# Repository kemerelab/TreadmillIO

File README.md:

# TreadmillIO

The TreadmillIO project (which needs a better name!) combines a simple USB-based
data IO module with a Python framework to provide a way to control behavioral
experiments using a simple YAML-based configuration scheme. One particular focus
of the project is to receive input from a rotary encoder to control auditory 
stimuli in a VR environment, but it is also convenient to use for experiments in
freely moving animals. In conjunction with the 
[PyRenderMaze project](http://github.com/ckemere/PyRenderMaze), a simple OpenGL-based
visual VR environment can easily be deployed. 

Some sample sound stimuli can be found in the [simple-sound-stimuli](https://github.com/kemerelab/simple-sound-stimuli)
repository.

### Requirements
The software is currently tested on Ubuntu Linux. The low-latency audio framework
relies on ALSA, which is Linux only, and the UVC WebCam capture interface has
only been tested on Linux. However, the project should otherwise work across
platforms. Pull requests for Windows or MAC compiling are welcome.

See the [installation instructions for the software framework](Documentation/Installation/INSTALL.md) to get up
and running.

### Configuring tasks controlled with the Treadmill-IO module

Some example [configuration files](Software/ExampleConfigFiles/) are available.

An example experimental setup using PschoPy-based stimuli is in the 
[simple-pyschopy-visual-task](https://github.com/kemerelab/simple-psychopy-visual-task)
project.

<!-- 
## Auditory VR Tasks

The file `AuditoryVR.py` generates a behavioral control system which has the following abilities:
  - Logs data acquired from the IO module
  - Processes incoming rotational encoder data to map wheel position to virtual position
  - Presents auditory stimuli in one of three modalities: background sounds, cues triggered by task states, and the sound of acoustic landmarks (which are amplitude modulated by their distance to the mouse in virtual space)
  - Responds appropriately to GPIO inputs (i.e., licks) based on task logic
  - Triggers GPIO output pulses as appropriate (i.e., to drive a syringe pump)

The controller is configued by a YAML file. An example configuration file, with explanatory comments is below.

```yaml
Info: # "Info" configuration options can be overridden by command line options
  MouseID: V1A1 # Used to name saved data file
  Note: '' # Added in a block at the start of saved data file
  Session: '' # This is added to default (date and time)
  TaskType: 3tones-change-classical

Preferences:
  HeartBeat: 250 # The interval at which a heart-beat info message is printed to screen (in ms) 

GPIO: # A list of GPIO pins used in the task
  Lick: # This is an arbitrary label used later to configure Reward
    Number: 3 # This is the pin number from the board
    Type: 'Input_Pulldown' # Pin type is either 'Inout' or 'Output'; special cases could be 'Input_Pulldown' or 'Input_Pullup' 
                           # (where the pull-down/pull-up resistors are enabled).
    Power: True # The 'Power' option is for 'Input' type GPIOs. It configures whether the Aux-GPIO is set to high, 
                # enabling the power channel of the audio jack.
  Reward:
    Number: 4
    Type: 'Output'
    Mirror: True # The 'Mirror' option is for 'Output' type GPIOs. It configures whether the associated Aux-GPIO pin is raised/lowered 
                 # whenver the GPIO itself is. The Aux-GPIO is connected to an LED, which allows for visualization of the GPIO state.

Maze:
  Type: 'VR' # VR or physical
  EncoderGain: 4096.0 # Encoder value per revolution
  Length: 150.0 # Length of the track. Presumably in cm units, but units don't really matter as long as they're consistent.
  WheelDiameter: 20.2 # Diameter of the wheel (presumably in cm units).
  TrackTransform: None # Not currently implemented.

AuditoryStimuli:
  AudioFileDirectory: '/home/ckemere/Code/TreadmillTracker/ClientSide/Tasks/HeadFixedTask/Sounds' # Directory in which file is stored
  MaximumNumberOfStimuli: 10 # Maximum number of auditory stimuli which follow in the StimuliList
  OscPort: 12345 # TCP port to use for OSC communication with jackminimix
  Defaults: # Default values for stimulus parameters
    Filename: '' # Possible to specify a default sound file
    BaselineGain: 0.0 # Volume of stimulus. Corresponds to the peak volume for a 'Localized' stimulus 
    OffGain: -90.0 # dB for stimulus off. -90 dB corresponds to 0 for jackminimix
    Type: 'Localized' # 'Localized' (landmark), 'Background', or 'Beep'
    Modulation: # Parameters which define how 'Localized' stimuli are spatially-modulated
      Type: Linear # Currently only 'Linear'
      CenterPosition: 0.0 # Position of Localized stimulus in VR space
      Width: 25 # cm in which sound is on (full width)
      #Rate: -20.0 # dB/cm - NOT CURRENTLY IMPLEMENTED BUT WOULD BE NICE FOR THE FUTURE
      CutoffGain: -60.0 #dB at cutoff - The change in gain as a function of position is determined
                        #  by the Width, BaselineGain, and CutoffGain parameters.
                        #  Note that true "Off" corresponds in our system to -90 dB.
                        #  So depending on SNR and perceptual ability, a CutoffGain greater
                        #  than that value might be noticeable.

  StimuliList:
    BackgroundSound: # This label is abitrary. In the case of "Beep" stimuli, it is used to configure Reward
      MinimixInputPort: 1 # jackminimix channel to use. By default, these will be auto-assigned if not specified
      MinimixChannel: 'left' # stereo audio channel whose volume should be controlled for this stimulus
      Type: 'Background' # Stimuli type - 'Localized', 'Background', or 'Beep'
      BaselineGain: -5.0
      Filename: 'pink_noise.wav'
      Color: 'pink' # Matplotlib color name used for visualization system
    Zone_1:
      CenterPosition: 12.5 
      Filename: 'tone_3kHz.wav'
      Modulation:
        Width: 10
      Color: 'lime'
    Zone_2:
      CenterPosition: 102.5 
      Filename: 'tone_11kHz.wav'
      Modulation:
        Width: 25
      Color: 'orange'
    RewardSound:
      Type: 'Beep'
      Filename: 'tone_11kHz.wav'
      Duration: 250 # ms

RewardZones: # Configuration of Reward locations
  RewardZoneList:
    Reward1: # Arbitrary label
      Type: 'Operant' # Currently either "Classical" or "Operant" corresponding to
                      # the definitions from psychology. Classical rewards are delivered
                      # at a particular location regardless of animal behavior. Operant
                      # rewards require a GPIO trigger (which we call a "Lick")
      LickPin: 'Lick' # Label of GPIO for sensor which triggers reward (in the case of Operant-style tasks)
      DispensePin: 'Reward' # (Required!) Label of GPIO for output pin which should trigger reward dispensing. 
      PumpRunTime: 1000 # How long to run the reward pump for. Note that this is also the duration
                        # of time that any associated Beep will be played.
      LickTimeout: 3000.0 # Time between reward availability
      MaxSequentialRewards: 50 # Number of times an animal that has stopped in the reward zone
                               # can be rewarded without having to exit and re-enter. After reaching
                               # this number of rewards, the animal has to pass through the "ResetZone"
                               # to reset reward availability.
      RewardZoneStart: 145 # The reward location begins at this point (in track coordinates).
                        # Note that since the track loops around, the end can be before the 
                        # beginning. (Order of beginning and end matter!)
      RewardZoneEnd: 30 # The reward zone ends at this point.
      ResetZoneStart: 100 # The start of location of the zone in the track that primes this reward location.
      ResetZoneEnd: 130 # The end of the reset zone.
      Color: 'black' # Visualization color of the reward zone.
      RewardSound: 'RewardSound' # The name of the auditory stimulus (of type "Beep") which should be played 
                                 # at the time of reward. This plays for the same duration of the pulse which
                                 # triggers the pump.

```

## StateMachine or VisualStimulus Tasks
The file `VisualStimulusExperiment.py` executes a state machine. Critically one of the states sends commands to a 
visual stimulus server started by executing `VisualStimulusServer.py`. Currently, the `VisualStimulusServer.py` file
creates a grey screen and presents a flashing checkerboard either in the left or right visual hemifields (calibrated
for a large 40" curved display). Following is an example YAML configuration file:

```
Info: # "Info" configuration options can be overridden by command line options
  MouseID: V1A1 # Used to name saved data file
  Note: '' # Added in a block at the start of saved data file
  Session: '' # This is added to default (date and time)
  TaskType: Moana Classical Conditioning

Preferences:
  HeartBeat: 1000 # The interval at which a heart-beat info message is printed to screen (in ms) 
  AudioFileDirectory: '/home/ckemere/Code/TreadmillTracker/ClientSide/Tasks/HeadFixedTask/Sounds' # Directory in which file is stored
  RandomSeed: 345
  VisualCommsPort: 5556
  LogCommands: True

GPIO: # A list of GPIO pins used in the task
  Camera: # This is an arbitrary label used later to configure Reward
    Number: 1 # This is the pin number from the board
    Type: 'Input_Pulldown' 
    Power: False
  Lick: # This is an arbitrary label used later to configure Reward
    Number: 2 # This is the pin number from the board
    Type: 'Input_Pulldown' # Pin type is either 'Input' or 'Output'; special cases could be 'Input_Pulldown' or 'Input_Pullup' 
                           # (where the pull-down/pull-up resistors are enabled).
    Power: True # The 'Power' option is for 'Input' type GPIOs. It configures whether the Aux-GPIO is set to high, 
                # enabling the power channel of the audio jack.
  ScreenLeft: # This is an arbitrary label used later to configure Reward
    Number: 3 # This is the pin number from the board
    Type: 'Input_Pulldown' 
    Power: True

  ScreenRight: # This is an arbitrary label used later to configure Reward
    Number: 4 # This is the pin number from the board
    Type: 'Input_Pulldown' 
    Power: True
  Reward:
    Number: 5
    Type: 'Output'
    Mirror: True # The 'Mirror' option is for 'Output' type GPIOs. It configures whether the associated Aux-GPIO pin is raised/lowered 
                 # whenver the GPIO itself is. The Aux-GPIO is connected to an LED, which allows for visualization of the GPIO state.
  GreyScreenIO:
    Number: 6
    Type: 'Output'
    Mirror: True 
  Disable7:
    Number: 7
    Type: 'Input_Disable'
  Disable8:
    Number: 8
    Type: 'Input_Disable'
  Disable9:
    Number: 9
    Type: 'Input_Disable'
  Disable10:
    Number: 10
    Type: 'Input_Disable'
  Disable11:
    Number: 11
    Type: 'Input_Disable'
  Disable12:
    Number: 12
    Type: 'Input_Disable'              

Maze:
  Type: 'StateMachine'

StateMachine: # Note - will start at the state below with the parameter "FirstState: True". Otherwise
              # the first state listed will be first.
  BlankScreen:
    Type: 'Visualization'
    Params:
      VisType: 'Fixed' # Can be either "Fixed" or "Random"
      Command: 'GREY'  # Command string sent to VisualStimulusServer
    NextState: 'Raise'
  Raise: # Raise a GPIO during the grey screen period
    Type: 'SetGPIO'
    Params:
      Pin: 'GreyScreenIO'
      Value: 1
    NextState: 'Intertrial'
  Intertrial:
    Type: 'Delay'
    Params:
      Duration: 'Fixed' # Can be either "Fixed" or "Random"
      Value: 5000
    NextState: 'Lower'
  Lower:
    Type: 'SetGPIO'
    Params:
      Pin: 'Reward'
      Value: 0
    NextState: 'StimulusPresentation'
  StimulusPresentation:
    FirstState: True    # Start statemachine here!s
    Type: 'Visualization'
    Params:
      VisType: 'Random' # Random visualizations are currently uniformly distributed based on the specified
                        # relative probabilities.
      Options:
        Right:
          Command: 'RIGHT' # Command sent to VisualStimulusServer
          Probability: 1   # Relative probabilitity. These will be normalized by the sum of all options.
        Left:
          Command: 'LEFT'
          Probability: 1
    NextState: 'StimulusPresentationDelay'
  StimulusPresentationDelay:
    Type: 'Delay'
    Params:
      Duration: 'Exponential' # Random duration is a bounded exponential.
      Rate: 1000              # Rate of exponential distribution in ms.
      Min: 2000               # Minimum value added to samples from distribution.
      Max: 4000               # All samples are truncated to this value.
    NextState: 'Reward'
  Reward:
      Type: 'Reward'   # We could also trigger reward by using the SetGPIO command. The "Reward" states
                       # are 'non-blocking', meaning the state machine will move along to the next state.
      NextState: 'BlankScreen'
      Params:
        DispensePin: 'Reward' # (Required!) Label of GPIO for output pin which should trigger reward dispensing. 
        PumpRunTime: 100 # How long to run the reward pump for. Note that this is also the duration
                          # of time that any associated Beep will be played.
        RewardSound: 'RewardSound' # The name of the auditory stimulus (of type "Beep") which should be played 
                              # at the time of reward. This plays for the same duration of the pulse which
                              # triggers the pump.

AuditoryStimuli:
  Defaults: # Default values for stimulus parameters
    Filename: '' # Possible to specify a default sound file
    BaselineGain: 0.0 # Volume of stimulus. Corresponds to the peak volume for a 'Localized' stimulus 
    Type: 'Localized' # 'Localized' (landmark), 'Background', or 'Beep'
    Modulation: # Parameters which define how 'Localized' stimuli are spatially-modulated
      Type: Linear # Currently only 'Linear'
      CenterPosition: 0.0 # Position of Localized stimulus in VR space
      Width: 25 # cm in which sound is on (full width)
      #Rate: -20.0 # dB/cm - NOT CURRENTLY IMPLEMENTED BUT WOULD BE NICE FOR THE FUTURE
      CutoffGain: -60.0 #dB at cutoff - The change in gain as a function of position is determined
                        #  by the Width, BaselineGain, and CutoffGain parameters.
                        #  Note that true "Off" corresponds in our system to -90 dB.
                        #  So depending on SNR and perceptual ability, a CutoffGain greater
                        #  than that value might be noticeable.  

  StimuliList:
    BackgroundSound: # This label is abitrary. In the case of "Beep" stimuli, it is used to configure Reward
      Type: 'Background' # Stimuli type - 'Localized', 'Background', or 'Beep'
      BaselineGain: -5.0
      Filename: 'pink_noise.wav'
      Color: 'pink' # Matplotlib color name used for visualization system
    RewardSound:
      Type: 'Beep'
      Filename: 'tone_11kHz.wav'
```

## Camera Window
At high resolution (>= 1080p) and frame rate, the multiprocessing queue (and underlying pipe) for the camera window struggles to pickle/unpickle the image data quickly enough to keep up with webcam stream (the write process, which uses raw jpeg data, doesn't seem to have this issue, presumably because serialization of the raw data is trivial). To manage this issue, we can specify a maximum buffer size for the queue. When exceeded, the queue will stop receiving new frames from the send end (`CameraInterface`) until the receive end (`CameraWindow`) has flushed the queue. This leads to some push and pull, periods of normal streaming interrupted by pauses, so there's room for improvement. An example config for a 1080p webcam:

```yaml
Cameras:
  Camera1:
    RecordVideo: True
    FilenameHeader: 'MouseCam1'
    Compress: False # Sets whether to transcode the MJPEG which comes from the camera to H.264
    CameraIndex: 0
    ResX: 1920 
    ResY: 1080
    FrameRate: 30
    BufferSizeFrames: 30 # maximum frames to buffer before flushing queue
    #BufferSizeMB: 500 # we could instead specify buffer size by MB
    Verbose: False
    CameraParams:
      Power Line frequency: 2, # 60 Hz
      Gain: 10
``` -->

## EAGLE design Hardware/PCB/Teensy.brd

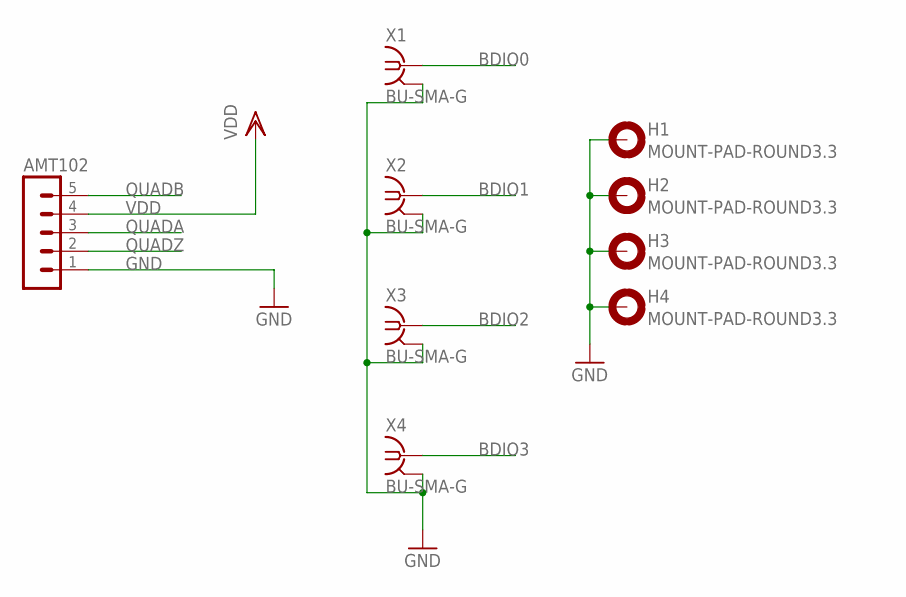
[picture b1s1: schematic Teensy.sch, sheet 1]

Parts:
AMT102: MA05-1
H1, H2, H3, H4: MOUNT-PAD-ROUND3.3; 3,3-PAD
X1, X2, X3, X4: BU-SMA-G

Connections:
BDIO0: X1.1; also elsewhere on the board
BDIO1: X2.1; also elsewhere on the board
BDIO2: X3.1; also elsewhere on the board
BDIO3: X4.1; also elsewhere on the board
GND: AMT102.1, H1.B3,3, H2.B3,3, H3.B3,3, H4.B3,3, X1.2, X1.3 (2), X1.4 (2), X1.5 (2), X2.2, X2.3 (2), X2.4 (2), X2.5 (2), X3.2, X3.3 (2), X3.4 (2), X3.5 (2), X4.2, X4.3 (2), X4.4 (2), X4.5 (2); also elsewhere on the board
QUADA: AMT102.3; also elsewhere on the board
QUADB: AMT102.5; also elsewhere on the board
QUADZ: AMT102.2; also elsewhere on the board
VDD: AMT102.4; also elsewhere on the board

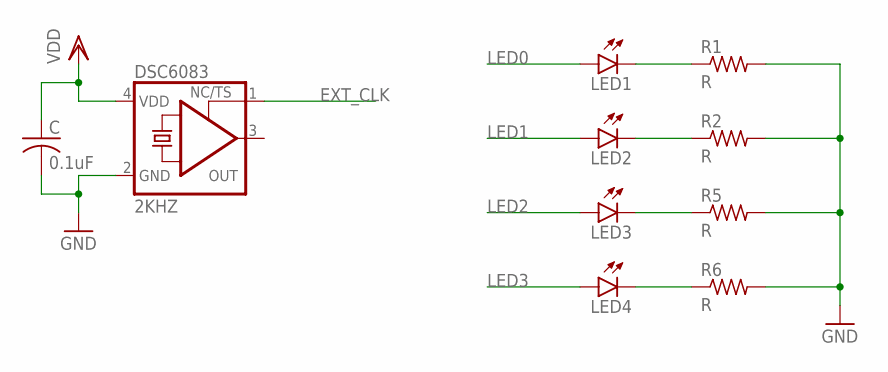
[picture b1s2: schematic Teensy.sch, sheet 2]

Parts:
C: 0.1uF; C0603
DSC6083: 2KHZ; 3.2X2.5_KXO-V96
LED1: LEDCHIPLED_0603; CHIPLED_0603
LED2, LED3, LED4: LEDCHIP-LED0603; CHIP-LED0603
R1, R2, R5, R6: R; R0603

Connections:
EXT_CLK: DSC6083.1 (TS); also elsewhere on the board
GND: C.2, DSC6083.2 (GND), R1.2, R2.2, R5.2, R6.2; also elsewhere on the board
LED0: LED1.A; also elsewhere on the board
LED1: LED2.A; also elsewhere on the board
LED2: LED3.A; also elsewhere on the board
LED3: LED4.A; also elsewhere on the board
unnamed: LED1.C, R1.1
unnamed: LED2.C, R2.1
unnamed: LED3.C, R5.1
unnamed: LED4.C, R6.1
VDD: C.1, DSC6083.4 (VDD); also elsewhere on the board

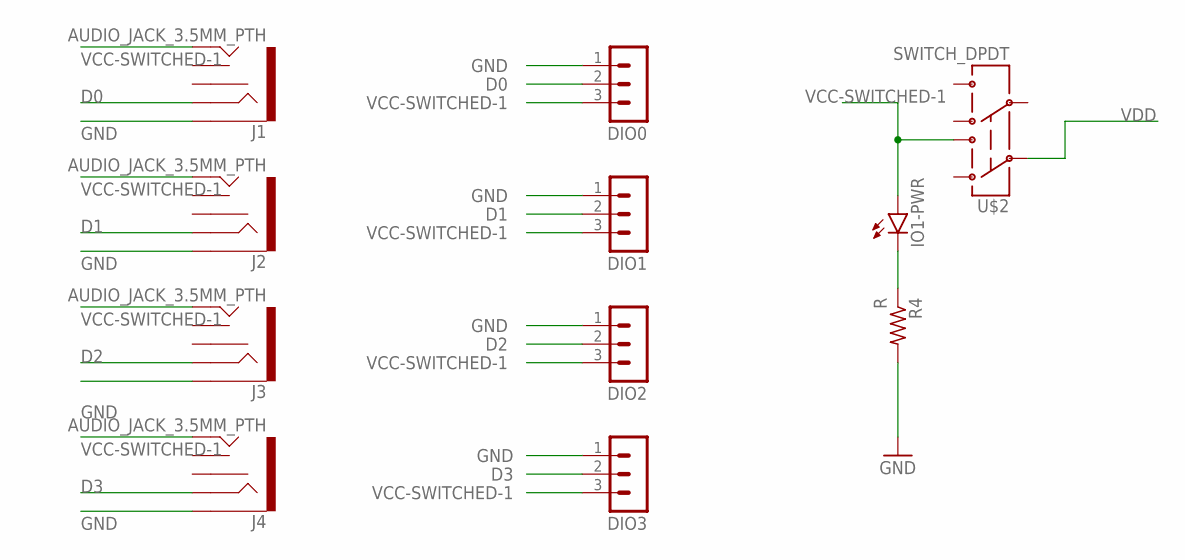
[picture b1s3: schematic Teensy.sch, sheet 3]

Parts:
DIO0, DIO1, DIO2, DIO3: MA03-1
IO1-PWR: LEDCHIP-LED0603; CHIP-LED0603
J1, J2, J3, J4: AUDIO_JACK_3.5MM_PTH; AUDIO-JACK
R4: R; R0603
U$2: SWITCH_DPDT; JS_DPDT_TH

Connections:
D0: DIO0.2, J1.RING; also elsewhere on the board
D1: DIO1.2, J2.RING; also elsewhere on the board
D2: DIO2.2, J3.RING; also elsewhere on the board
D3: DIO3.2, J4.RING; also elsewhere on the board
GND: DIO0.1, DIO1.1, DIO2.1, DIO3.1, J1.SLEEVE, J2.SLEEVE, J3.SLEEVE, J4.SLEEVE, R4.2; also elsewhere on the board
unnamed: IO1-PWR.C, R4.1
VCC-SWITCHED-1: DIO0.3, DIO1.3, DIO2.3, DIO3.3, IO1-PWR.A, J1.TIP, J2.TIP, J3.TIP, J4.TIP, U$2.3
VDD: U$2.2; also elsewhere on the board

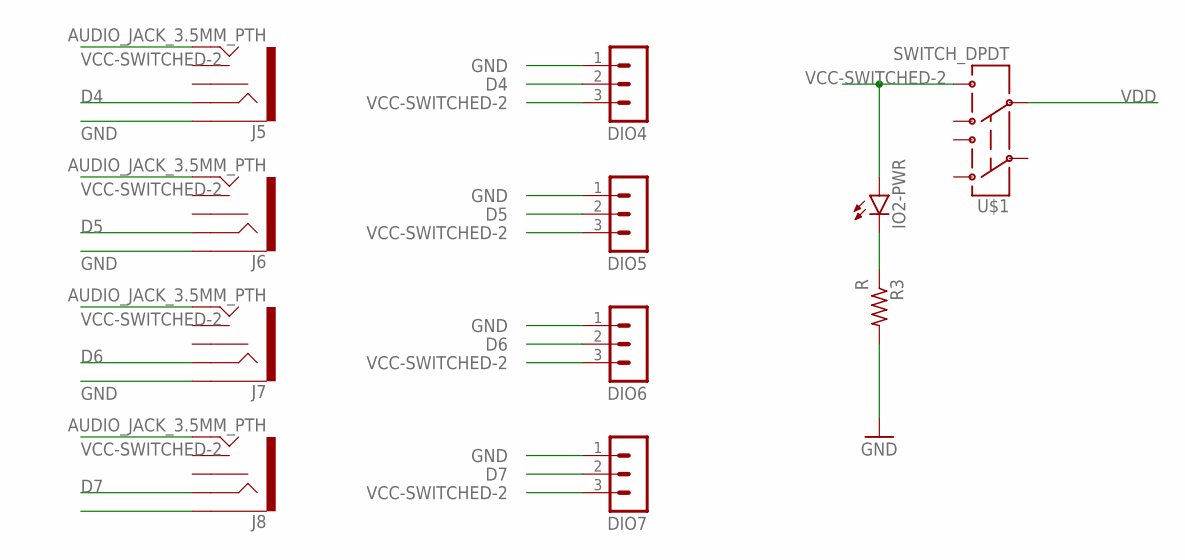
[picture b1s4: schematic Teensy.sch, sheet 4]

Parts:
DIO4, DIO5, DIO6, DIO7: MA03-1
IO2-PWR: LEDCHIP-LED0603; CHIP-LED0603
J5, J6, J7, J8: AUDIO_JACK_3.5MM_PTH; AUDIO-JACK
R3: R; R0603
U$1: SWITCH_DPDT; JS_DPDT_TH

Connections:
D4: DIO4.2, J5.RING; also elsewhere on the board
D5: DIO5.2, J6.RING; also elsewhere on the board
D6: DIO6.2, J7.RING; also elsewhere on the board
D7: DIO7.2, J8.RING; also elsewhere on the board
GND: DIO4.1, DIO5.1, DIO6.1, DIO7.1, J5.SLEEVE, J6.SLEEVE, J7.SLEEVE, J8.SLEEVE, R3.2; also elsewhere on the board
unnamed: IO2-PWR.C, R3.1
VCC-SWITCHED-2: DIO4.3, DIO5.3, DIO6.3, DIO7.3, IO2-PWR.A, J5.TIP, J6.TIP, J7.TIP, J8.TIP, U$1.6
VDD: U$1.5; also elsewhere on the board

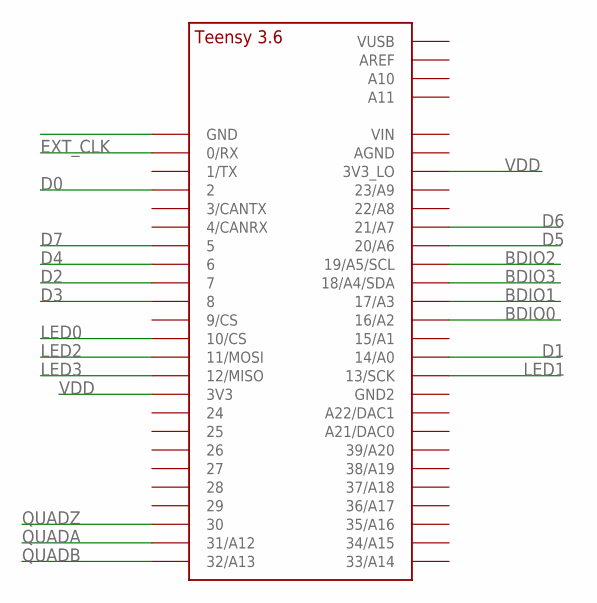
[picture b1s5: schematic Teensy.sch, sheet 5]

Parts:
U$3: TEENSY_3.5/3.6_BASIC

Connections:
BDIO0: U$3.16/A2; also elsewhere on the board
BDIO1: U$3.17/A3; also elsewhere on the board
BDIO2: U$3.19/A5/SCL; also elsewhere on the board
BDIO3: U$3.18/A4/SDA; also elsewhere on the board
D0: U$3.2; also elsewhere on the board
D1: U$3.14/A0; also elsewhere on the board
D2: U$3.7; also elsewhere on the board
D3: U$3.8; also elsewhere on the board
D4: U$3.6; also elsewhere on the board
D5: U$3.20/A6; also elsewhere on the board
D6: U$3.21/A7; also elsewhere on the board
D7: U$3.5; also elsewhere on the board
EXT_CLK: U$3.0/RX; also elsewhere on the board
GND: U$3.GND; also elsewhere on the board
LED0: U$3.10/CS; also elsewhere on the board
LED1: U$3.13/SCK; also elsewhere on the board
LED2: U$3.11/MOSI; also elsewhere on the board
LED3: U$3.12/MISO; also elsewhere on the board
QUADA: U$3.31/A12; also elsewhere on the board
QUADB: U$3.32/A13; also elsewhere on the board
QUADZ: U$3.30; also elsewhere on the board
VDD: U$3.3V3, U$3.3V3_LO; also elsewhere on the board

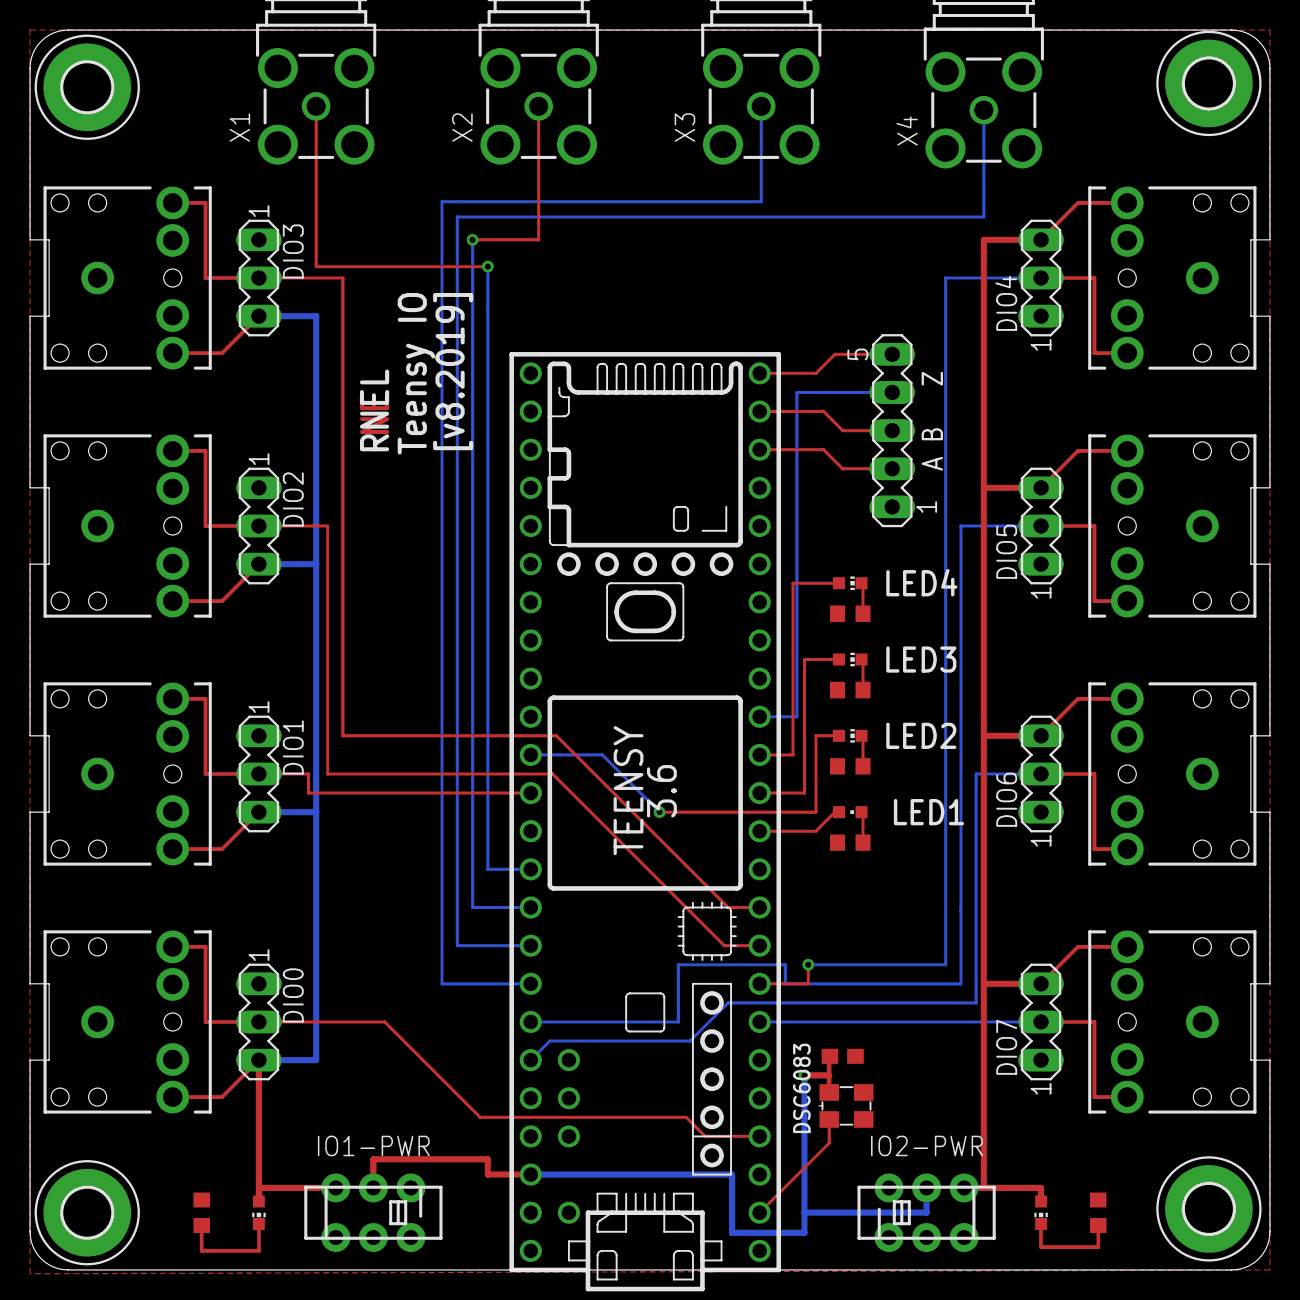
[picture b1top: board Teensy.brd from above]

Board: 2 copper layers, 82.5 x 82.5 mm, 42 parts (0 on the bottom side), 30 nets.

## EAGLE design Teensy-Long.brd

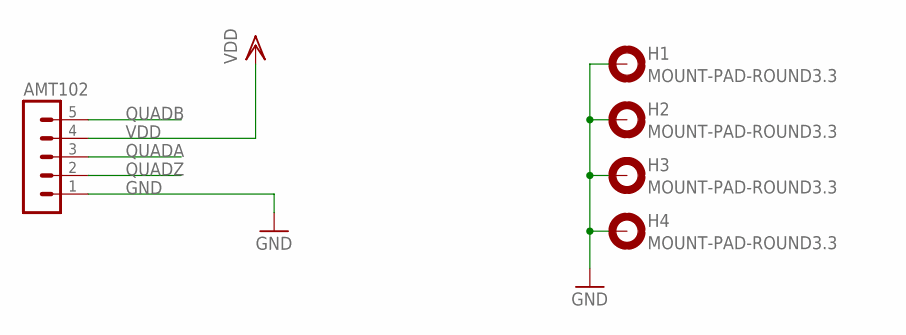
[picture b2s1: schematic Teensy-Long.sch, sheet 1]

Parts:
AMT102: MA05-1
H1, H2, H3, H4: MOUNT-PAD-ROUND3.3; 3,3-PAD

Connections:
GND: AMT102.1, H1.B3,3, H2.B3,3, H3.B3,3, H4.B3,3; also elsewhere on the board
QUADA: AMT102.3; also elsewhere on the board
QUADB: AMT102.5; also elsewhere on the board
QUADZ: AMT102.2; also elsewhere on the board
VDD: AMT102.4; also elsewhere on the board

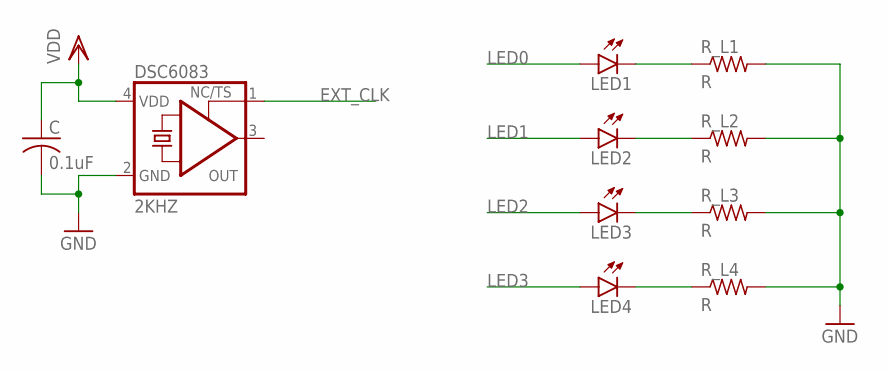
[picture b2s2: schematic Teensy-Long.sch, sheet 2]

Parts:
C: 0.1uF; C0603
DSC6083: 2KHZ; 3.2X2.5_KXO-V96
LED1, LED2, LED3, LED4: LEDCHIP-LED0603; CHIP-LED0603
R_L1, R_L2, R_L3, R_L4: R; R0603

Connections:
EXT_CLK: DSC6083.1 (TS); also elsewhere on the board
GND: C.2, DSC6083.2 (GND), R_L1.2, R_L2.2, R_L3.2, R_L4.2; also elsewhere on the board
LED0: LED1.A; also elsewhere on the board
LED1: LED2.A; also elsewhere on the board
LED2: LED3.A; also elsewhere on the board
LED3: LED4.A; also elsewhere on the board
unnamed: LED1.C, R_L1.1
unnamed: LED2.C, R_L2.1
unnamed: LED3.C, R_L3.1
unnamed: LED4.C, R_L4.1
VDD: C.1, DSC6083.4 (VDD); also elsewhere on the board

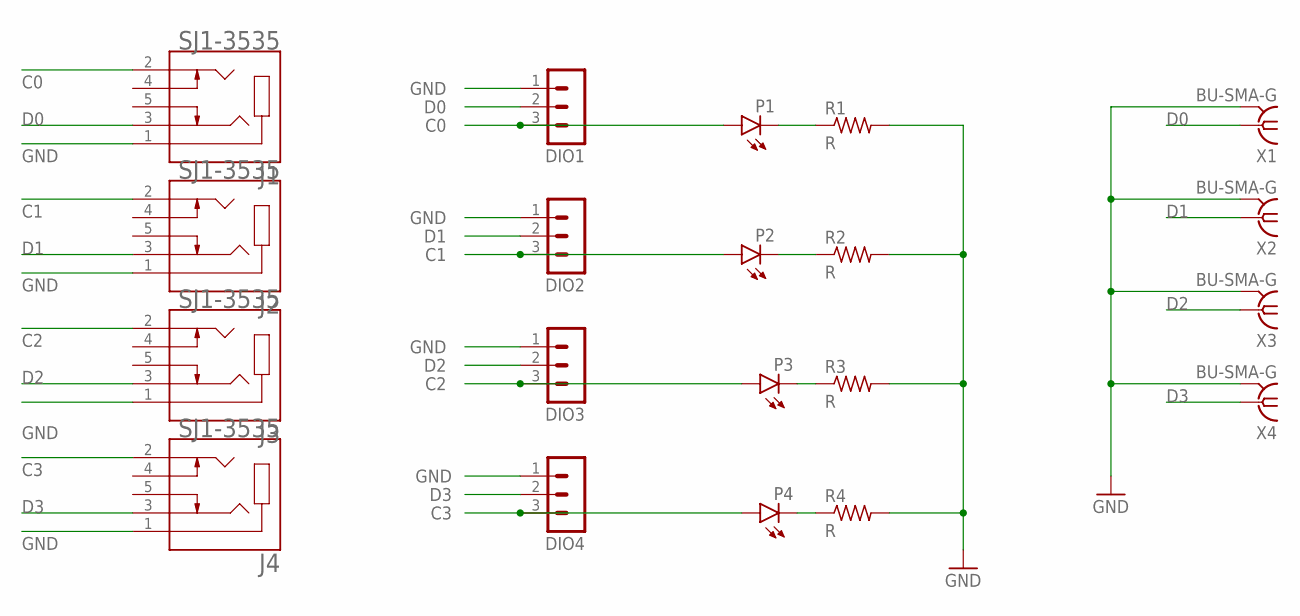
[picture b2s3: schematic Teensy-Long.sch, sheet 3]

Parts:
DIO1, DIO2, DIO3, DIO4: MA03-1
J1, J2, J3, J4: SJ1-3535; CUI_SJ1-3535
P1, P2, P3, P4: LEDCHIP-LED0603; CHIP-LED0603
R1, R2, R3, R4: R; R0603
X1, X2, X3, X4: BU-SMA-G

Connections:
C0: DIO1.3, J1.2, P1.A; also elsewhere on the board
C1: DIO2.3, J2.2, P2.A; also elsewhere on the board
C2: DIO3.3, J3.2, P3.A; also elsewhere on the board
C3: DIO4.3, J4.2, P4.A; also elsewhere on the board
D0: DIO1.2, J1.3, X1.1; also elsewhere on the board
D1: DIO2.2, J2.3, X2.1; also elsewhere on the board
D2: DIO3.2, J3.3, X3.1; also elsewhere on the board
D3: DIO4.2, J4.3, X4.1; also elsewhere on the board
GND: DIO1.1, DIO2.1, DIO3.1, DIO4.1, J1.1, J2.1, J3.1, J4.1, R1.2, R2.2, R3.2, R4.2, X1.2, X1.3 (2), X1.4 (2), X1.5 (2), X2.2, X2.3 (2), X2.4 (2), X2.5 (2), X3.2, X3.3 (2), X3.4 (2), X3.5 (2), X4.2, X4.3 (2), X4.4 (2), X4.5 (2); also elsewhere on the board
unnamed: P1.C, R1.1
unnamed: P2.C, R2.1
unnamed: P3.C, R3.1
unnamed: P4.C, R4.1

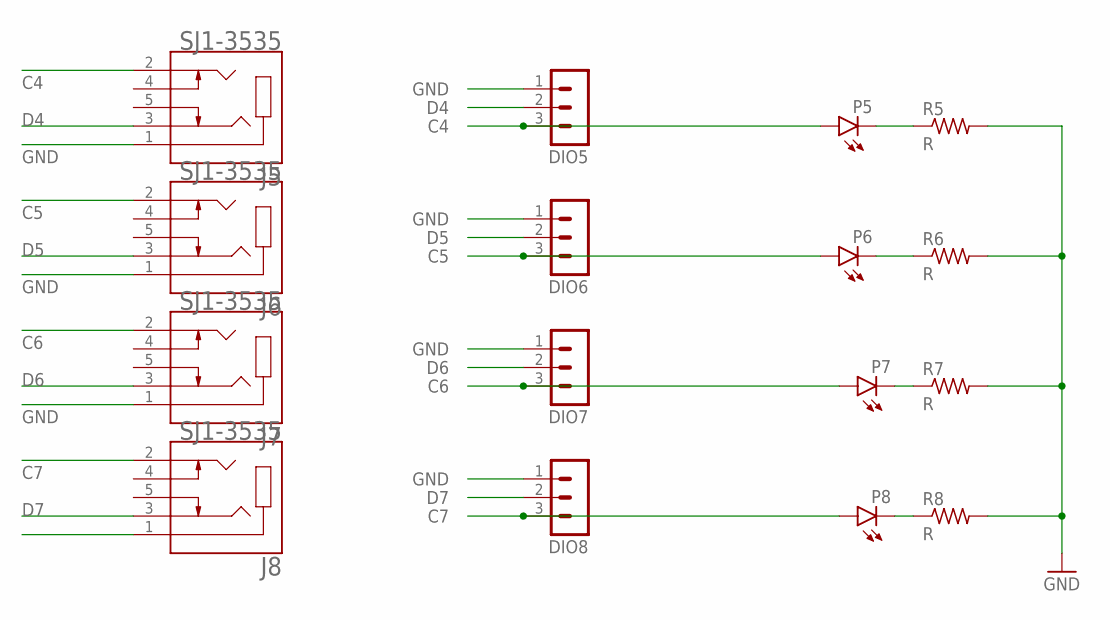
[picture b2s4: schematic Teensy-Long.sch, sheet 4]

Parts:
DIO5, DIO6, DIO7, DIO8: MA03-1
J5, J6, J7, J8: SJ1-3535; CUI_SJ1-3535
P5, P6, P7, P8: LEDCHIP-LED0603; CHIP-LED0603
R5, R6, R7, R8: R; R0603

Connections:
C4: DIO5.3, J5.2, P5.A; also elsewhere on the board
C5: DIO6.3, J6.2, P6.A; also elsewhere on the board
C6: DIO7.3, J7.2, P7.A; also elsewhere on the board
C7: DIO8.3, J8.2, P8.A; also elsewhere on the board
D4: DIO5.2, J5.3; also elsewhere on the board
D5: DIO6.2, J6.3; also elsewhere on the board
D6: DIO7.2, J7.3; also elsewhere on the board
D7: DIO8.2, J8.3; also elsewhere on the board
GND: DIO5.1, DIO6.1, DIO7.1, DIO8.1, J5.1, J6.1, J7.1, J8.1, R5.2, R6.2, R7.2, R8.2; also elsewhere on the board
unnamed: P5.C, R5.1
unnamed: P6.C, R6.1
unnamed: P7.C, R7.1
unnamed: P8.C, R8.1

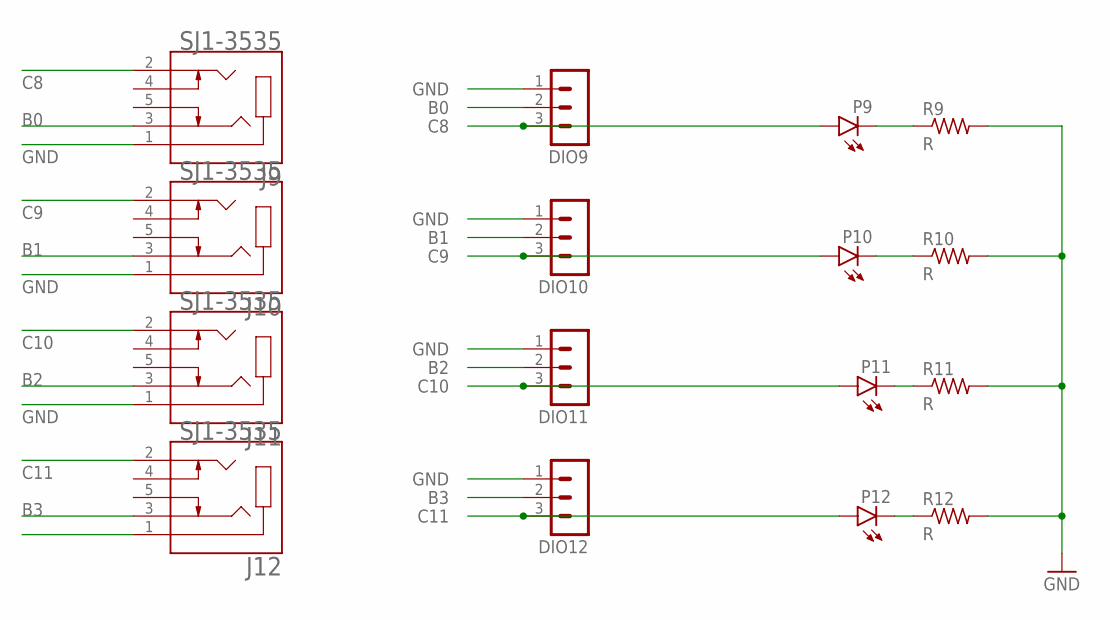
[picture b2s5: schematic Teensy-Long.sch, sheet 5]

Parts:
DIO9, DIO10, DIO11, DIO12: MA03-1
J9, J10, J11, J12: SJ1-3535; CUI_SJ1-3535
P9, P10, P11, P12: LEDCHIP-LED0603; CHIP-LED0603
R9, R10, R11, R12: R; R0603

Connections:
B0: DIO9.2, J9.3; also elsewhere on the board
B1: DIO10.2, J10.3; also elsewhere on the board
B2: DIO11.2, J11.3; also elsewhere on the board
B3: DIO12.2, J12.3; also elsewhere on the board
C8: DIO9.3, J9.2, P9.A; also elsewhere on the board
C9: DIO10.3, J10.2, P10.A; also elsewhere on the board
C10: DIO11.3, J11.2, P11.A; also elsewhere on the board
C11: DIO12.3, J12.2, P12.A; also elsewhere on the board
GND: DIO9.1, DIO10.1, DIO11.1, DIO12.1, J9.1, J10.1, J11.1, J12.1, R9.2, R10.2, R11.2, R12.2; also elsewhere on the board
unnamed: P9.C, R9.1
unnamed: P10.C, R10.1
unnamed: P11.C, R11.1
unnamed: P12.C, R12.1

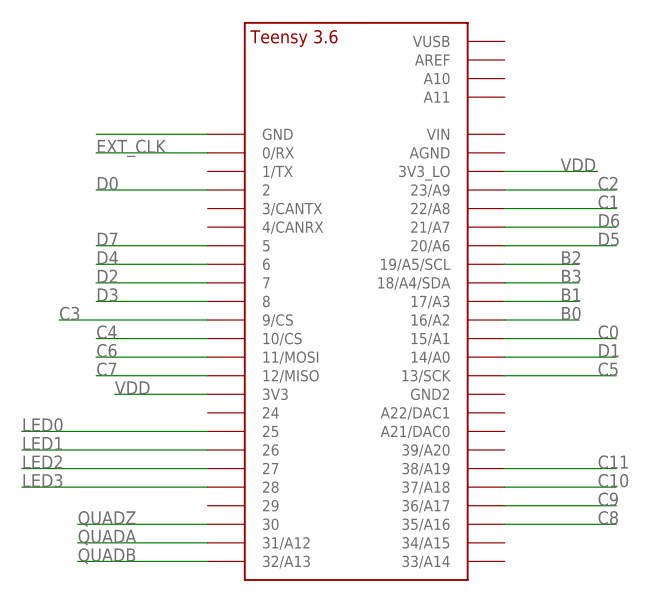
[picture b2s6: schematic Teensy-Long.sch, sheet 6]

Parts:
U$3: TEENSY_3.5/3.6_BASIC

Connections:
B0: U$3.16/A2; also elsewhere on the board
B1: U$3.17/A3; also elsewhere on the board
B2: U$3.19/A5/SCL; also elsewhere on the board
B3: U$3.18/A4/SDA; also elsewhere on the board
C0: U$3.15/A1; also elsewhere on the board
C1: U$3.22/A8; also elsewhere on the board
C2: U$3.23/A9; also elsewhere on the board
C3: U$3.9/CS; also elsewhere on the board
C4: U$3.10/CS; also elsewhere on the board
C5: U$3.13/SCK; also elsewhere on the board
C6: U$3.11/MOSI; also elsewhere on the board
C7: U$3.12/MISO; also elsewhere on the board
C8: U$3.35/A16; also elsewhere on the board
C9: U$3.36/A17; also elsewhere on the board
C10: U$3.37/A18; also elsewhere on the board
C11: U$3.38/A19; also elsewhere on the board
D0: U$3.2; also elsewhere on the board
D1: U$3.14/A0; also elsewhere on the board
D2: U$3.7; also elsewhere on the board
D3: U$3.8; also elsewhere on the board
D4: U$3.6; also elsewhere on the board
D5: U$3.20/A6; also elsewhere on the board
D6: U$3.21/A7; also elsewhere on the board
D7: U$3.5; also elsewhere on the board
EXT_CLK: U$3.0/RX; also elsewhere on the board
GND: U$3.GND; also elsewhere on the board
LED0: U$3.25; also elsewhere on the board
LED1: U$3.26; also elsewhere on the board
LED2: U$3.27; also elsewhere on the board
LED3: U$3.28; also elsewhere on the board
QUADA: U$3.31/A12; also elsewhere on the board
QUADB: U$3.32/A13; also elsewhere on the board
QUADZ: U$3.30; also elsewhere on the board
VDD: U$3.3V3, U$3.3V3_LO; also elsewhere on the board

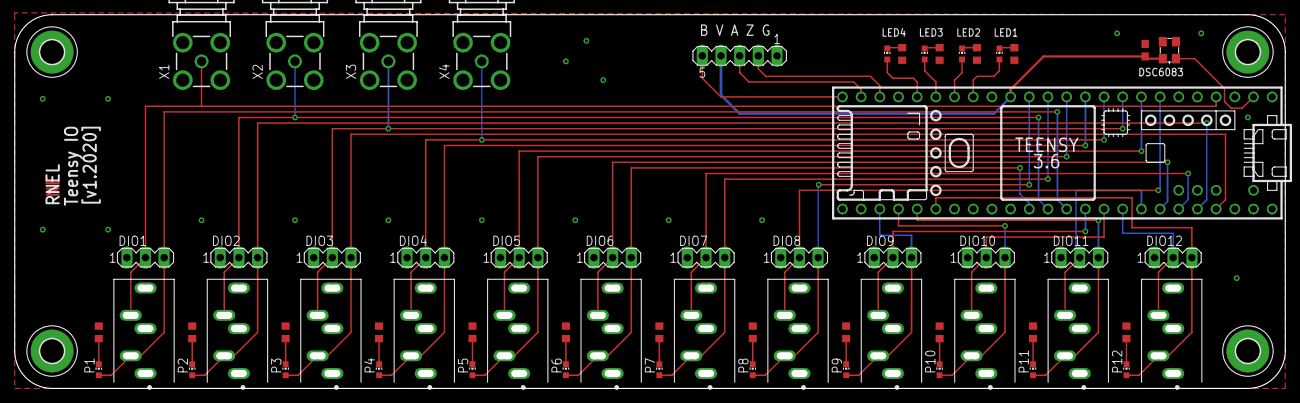
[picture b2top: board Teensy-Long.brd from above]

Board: 2 copper layers, 172.7 x 50.8 mm, 68 parts (0 on the bottom side), 50 nets.

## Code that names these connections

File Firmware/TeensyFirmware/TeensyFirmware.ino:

#define CLOCK_PIN 0 // B16

#define QUADZ 30 // C11
#define QUADA 31 // E0
#define QUADB 32 // B18

#define D0 2 // D0
#define D1 14 // ...
#define D2 7
#define D3 8
#define D4 6
#define D5 20
#define D6 21
#define D7 5 // D7
#define D8 16 // B0
#define D9 17 // B1
#define D10 19 // B2
#define D11 18 // B3

#define C0 15 // C0
#define C1 22 // ..
#define C2 23
#define C3 9
#define C4 10
#define C5 13
#define C6 11
#define C7 12 // C7
#define C8 35 // C8
#define C9 36 // C9
#define C10 37 // C10
#define C11 38 // C11


#define LED0 25 // A5
#define LED1 26 // A14
#define LED2 27 // A15
#define LED3 28 // A16

#define ENCODER_OPTIMIZE_INTERRUPTS // this messes up attachInterrupts
#include <Encoder.h>


IntervalTimer sendDataTimer;

Encoder wheelPosition(QUADA, QUADB);

uint32_t ledState = 0x11111111;

struct _TreadmillDataStruct {
  char StartChar;
  char DataLength;
//  uint16_t MasterClockLow;
//  uint16_t MasterClockHigh;
  uint32_t MasterClock;
  int16_t  EncoderTicks;
  int32_t  UnwrappedEncoderTicks;
  uint8_t  GPIO;
  char EndChar;
} __attribute__((packed));
typedef struct _TreadmillDataStruct TreadmillDataStruct;

TreadmillDataStruct TreadmillData;

volatile uint32_t MasterClock = 0;

boolean SerialTransmitFlag = false;

// ISR routine for FlexTimer1 Module
extern "C" void ftm1_isr(void) {
  if ((FTM1_SC & FTM_SC_TOF) != 0) {  //read the timer overflow flag (TOF in FTM1_SC)
    MasterClock++;
    FTM1_SC &= ~FTM_SC_TOF;           //if set, clear overflow flag

    if ((MasterClock & 0x01) == 0)
      SerialTransmitFlag  = true;
  }
}

void sendData() {

  if (Serial.dtr()) {
    TreadmillData.MasterClock = MasterClock;
    TreadmillData.GPIO = GPIOD_PDIR;
    TreadmillData.UnwrappedEncoderTicks = wheelPosition.read();
    Serial.write((char *) &TreadmillData, sizeof(TreadmillDataStruct));
    Serial.flush();
  }

}


void setup() {
  pinMode(LED0, OUTPUT);
  pinMode(LED1, OUTPUT);
  pinMode(LED2, OUTPUT);
  pinMode(LED3, OUTPUT);
  digitalWrite(LED0,0);
  digitalWrite(LED1,0);
  digitalWrite(LED2,0);
  digitalWrite(LED3,0);

  pinMode(D0, INPUT);
  pinMode(D1, INPUT);
  pinMode(D2, INPUT);
  pinMode(D3, INPUT);
  pinMode(D4, OUTPUT);
  pinMode(D5, OUTPUT);
  pinMode(D6, OUTPUT);
  pinMode(D7, OUTPUT);
  pinMode(D8, OUTPUT);
  pinMode(D9, OUTPUT);
  pinMode(D10, OUTPUT);
  pinMode(D11, OUTPUT);

  pinMode(C0, OUTPUT);
  pinMode(C1, OUTPUT);
  pinMode(C2, OUTPUT);
  pinMode(C3, OUTPUT);
  pinMode(C4, OUTPUT);
  pinMode(C5, OUTPUT);
  pinMode(C6, OUTPUT);
  pinMode(C7, OUTPUT);
  pinMode(C8, INPUT);
  pinMode(C9, INPUT);
  pinMode(C10, INPUT);
  pinMode(C11, INPUT);
  digitalWrite(C0,1);
  digitalWrite(C1,1);
  digitalWrite(C2,1);
  digitalWrite(C3,1);
  digitalWrite(C4,0);
  digitalWrite(C5,0);
  digitalWrite(C6,0);
  digitalWrite(C7,0);


  digitalWrite(D4, 0);
  digitalWrite(D5, 0);
  digitalWrite(D6, 0);
  digitalWrite(D7, 0);
  digitalWrite(D8, 0);
  digitalWrite(D9, 0);
  digitalWrite(D10, 0);
  digitalWrite(D11, 0);
  
  TreadmillData.StartChar = 'E';
  TreadmillData.EndChar = '\n';
  TreadmillData.DataLength = sizeof(TreadmillDataStruct);

  /* 
   *  Set up FTM timer module which connects to external 2kHz
   *   clock for master timing. The clock is set up both to increment
   *   the master clock counter. When it overflows, this also triggers
   *   the high 16 bits of the master clock to increment.
   *   
   *   Note that unlike with the MSP430, we can't independently set
   *   a second interrupt to trigger every millisecond to drive serial
   *   data transmission, so we'll just use the Teensy for that.
   *   
   */
  CORE_PIN0_CONFIG = PORT_PCR_MUX(4);
  NVIC_DISABLE_IRQ(IRQ_FTM1);
  FTM1_SC = 0;
  FTM1_CNT = 0;
  FTM1_MOD = 0x1; // set to overflow every two ticks (1 kHz)
  FTM1_SC = FTM_SC_CLKS(3) + FTM_SC_PS(0) + FTM_SC_TOIE; // External clock input
  NVIC_ENABLE_IRQ(IRQ_FTM1);
  
  Serial.begin(256000);
  //sendDataTimer.begin(sendData, 2000); // 2 ms
}

void sequenceLEDs(void) {
  static int led = 0;
  static int count = 50;
  
  if (count-- == 0) {
    count = 50;
  }
  else {
    return;
  }
  
  
  switch (led) {
    case 0:
      digitalWrite(LED0, 1);
      digitalWrite(LED3, 0);
      led = 1;
      break;
    case 1:
      digitalWrite(LED1, 1);
      digitalWrite(LED0, 0);
      led = 2;
      break;
    case 2:
      digitalWrite(LED2, 1);
      digitalWrite(LED1, 0);
      led = 3;
      break;
    case 3:
      digitalWrite(LED3, 1);
      digitalWrite(LED2, 0);
      led = 0;
      break;
  }
}

void loop() {
  
  interrupts();
  if (SerialTransmitFlag) {
    sendData();
    SerialTransmitFlag = false; // I'm worried about the case where I set this right when the timer is trying to wake us up.
                                // But I guess in that case, it would indicate we're on the hairy edge of stability, which is bad anyway.

    sequenceLEDs();
  }
  
  if (Serial.available()) {
    uint8_t incomingByte = Serial.read();  // will not be -1
    GPIOD_PDOR = incomingByte & 0xF0; // Recalling that higher order bits are output
    GPIOC_PDOR = incomingByte & 0xF0; // Recalling that higher order bits are output
  }
}

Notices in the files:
Hardware/PCB/Teensy.brd:
(c) 2019
Teensy-Long.brd:
(c) 2020
parts and their libraries:
crystal-geyer_V1_0: Copyright: Geyer-Electronic
SparkFun-Connectors: Licensing: Creative Commons ShareAlike 4.0 International - https://creativecommons.org/licenses/by-sa/4.0
